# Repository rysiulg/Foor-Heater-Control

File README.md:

Own implementation
Foor Heater Control
with PCB based on triac and optotriac control

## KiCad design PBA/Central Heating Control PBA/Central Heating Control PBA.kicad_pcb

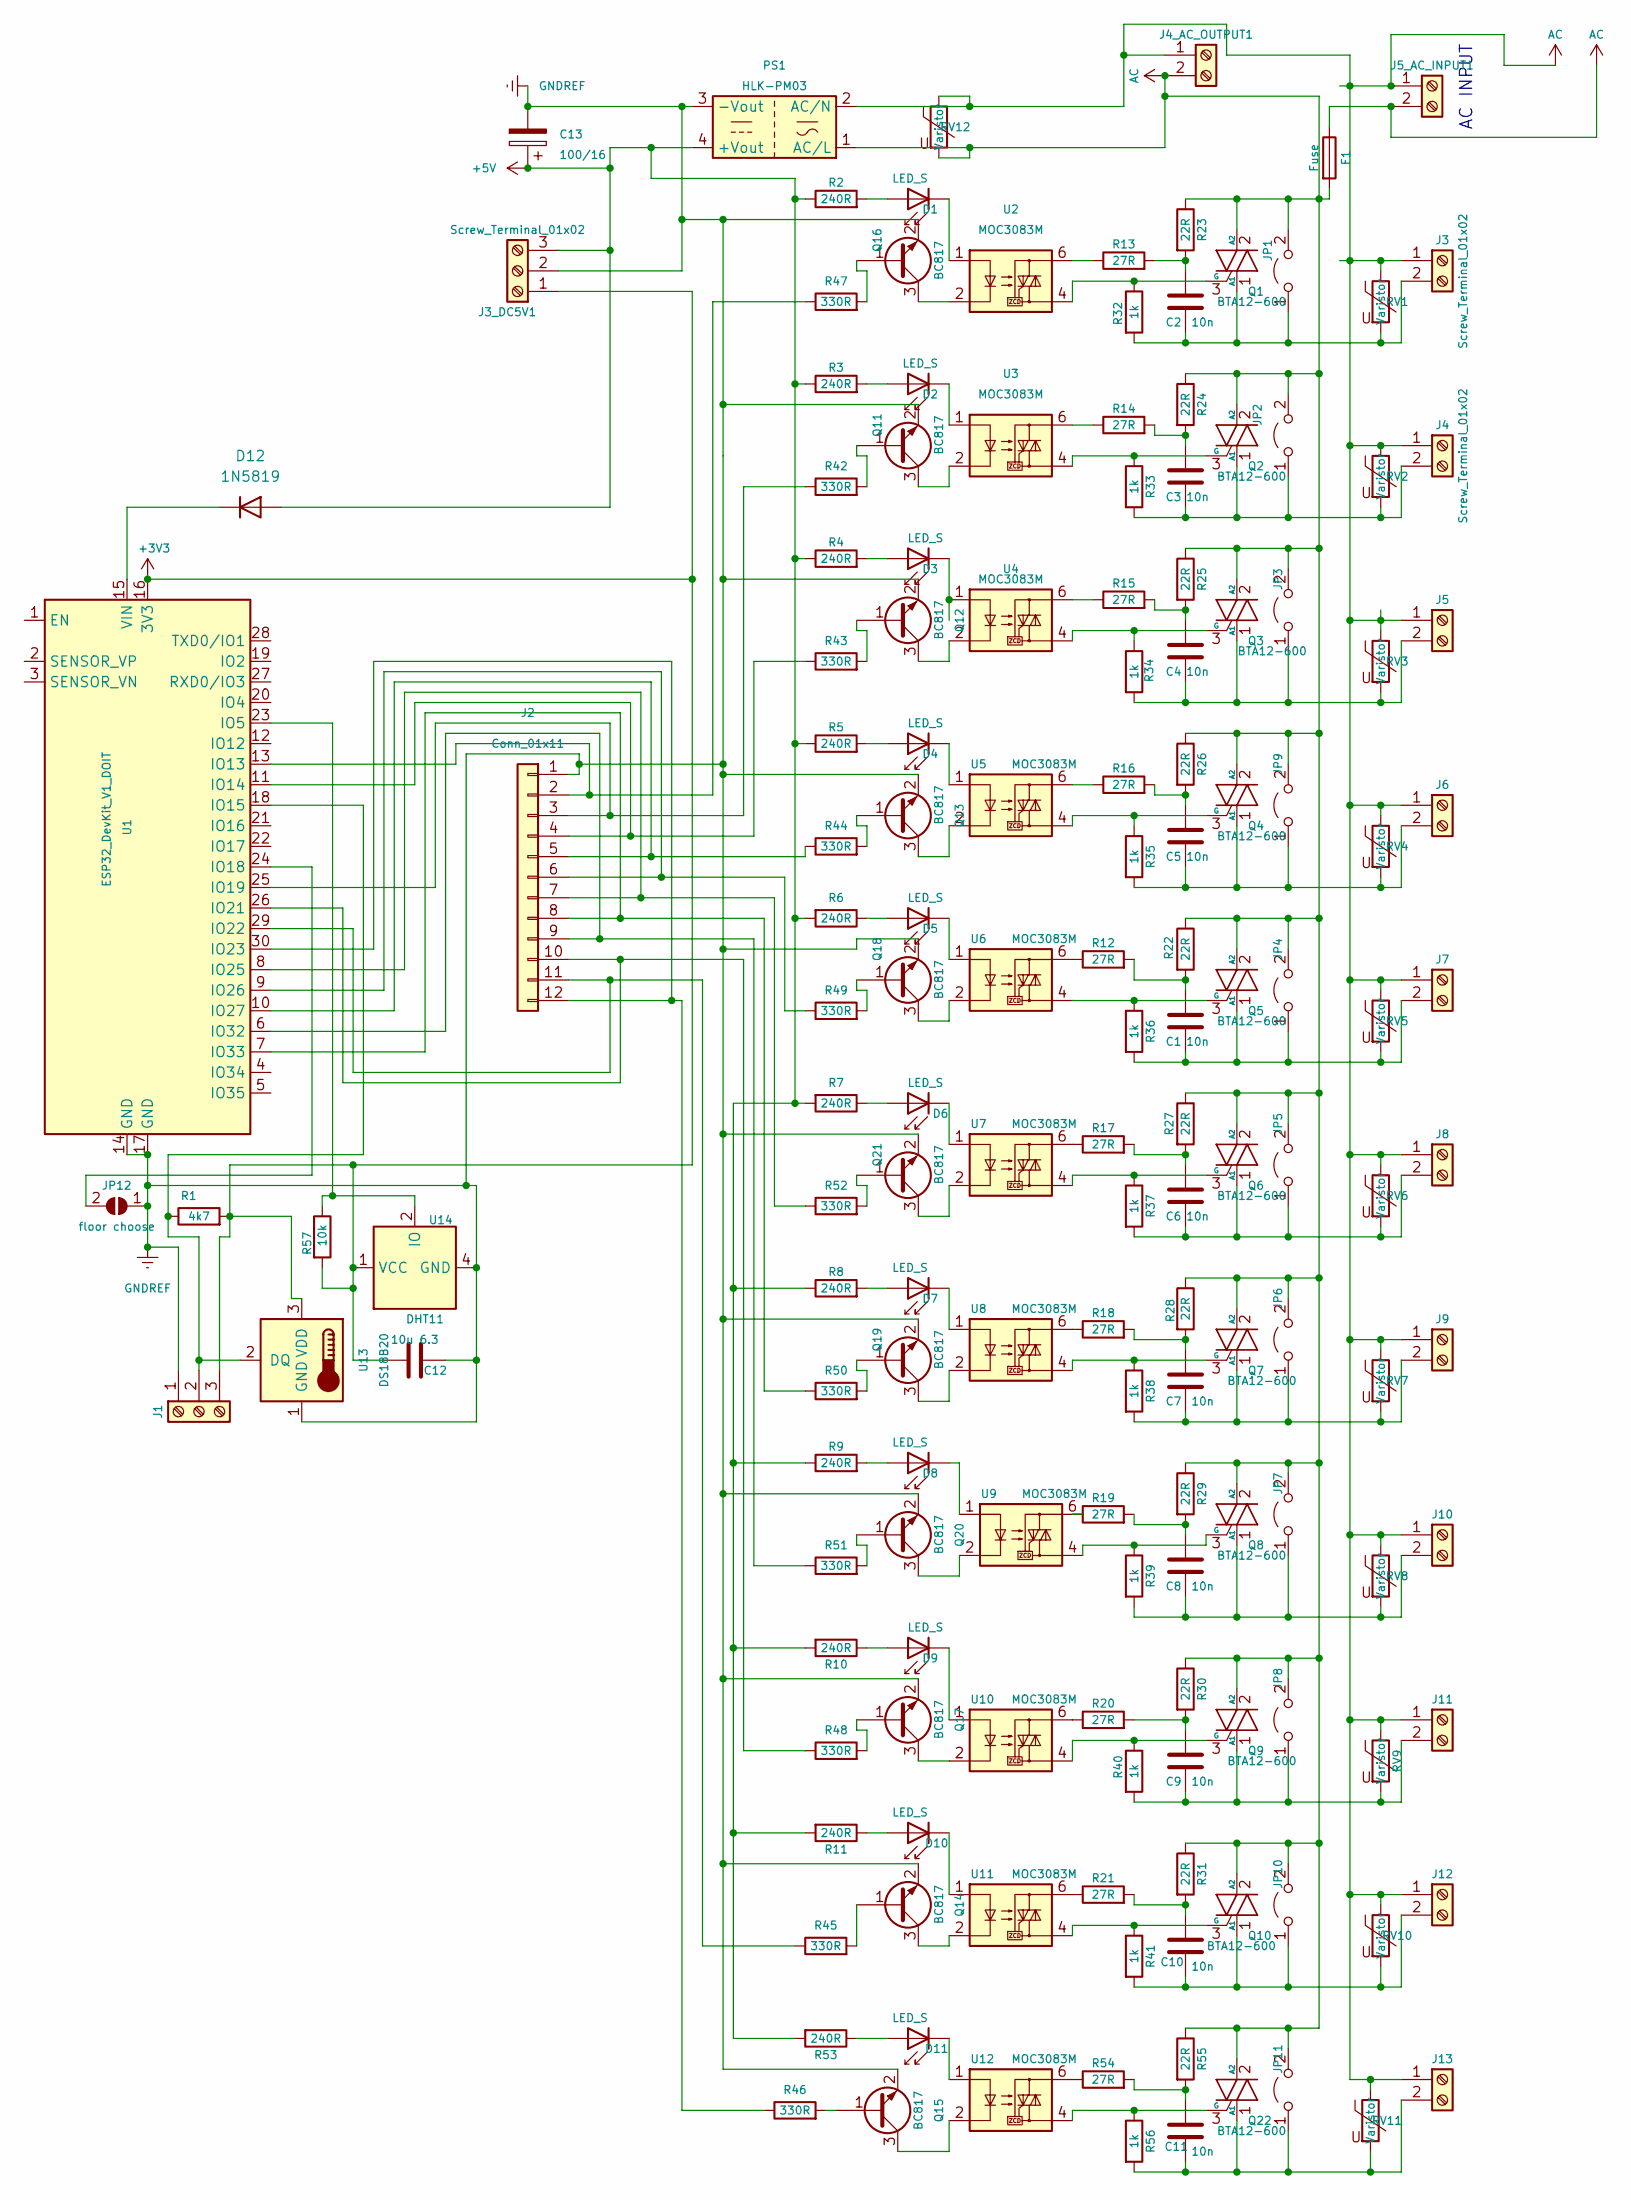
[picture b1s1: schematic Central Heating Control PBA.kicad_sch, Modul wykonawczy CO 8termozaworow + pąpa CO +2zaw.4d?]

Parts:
C1, C2, C3, C4, C5, C6, C7, C8, C9, C10, C11: 10n; C_Rect_L19.0mm_W7.0mm_P15.00mm_MKS4
C12: 10u 6.3; C_0805_2012Metric_Pad1.18x1.45mm_HandSolder
C13: 100/16; CP_Elec_6.3x5.9
D1, D2, D3, D4, D5, D6, D7, D8, D9, D10, D11: LED_S; LED_Rectangular_W3.0mm_H2.0mm
D12: 1N5819; D_SOD-123
F1: Fuse; Fuseholder_Littelfuse_100_series_5x20mm
J1: Screw_Terminal_01x03; TerminalBlock_MetzConnect_Type086_RT03403HBLC_1x03_P3.81mm_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
J2: Conn_01x11; PinHeader_1x12_P2.54mm_Vertical
J3, J4, J5, J6, J7, J8, J9, J10, J11, J12, J13: Screw_Terminal_01x02; TerminalBlock_MetzConnect_Type171_RT13702HBWC_1x02_P7.50mm_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
J3_DC5V1: Screw_Terminal_01x02; TerminalBlock_MetzConnect_Type073_RT02603HBLU_1x03_P5.08mm_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
J4_AC_OUTPUT1, J5_AC_INPUT1: Screw_Terminal_01x02; TerminalBlock_MetzConnect_Type101_RT01602HBWC_1x02_P5.08mm_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
JP1, JP2, JP3, JP4, JP5, JP6, JP7, JP8, JP9, JP10, JP11: Jumper_2_Open; PinSocket_1x02_P2.54mm_Vertical
JP12: floor choose; SolderJumper-2_P1.3mm_Open_TrianglePad1.0x1.5mm
PS1: HLK-PM03; Converter_ACDC_HiLink_HLK-PMxx
Q1, Q2, Q3, Q4, Q5, Q6, Q7, Q8, Q9, Q10, Q22: BTA12-600; TO-220-3_Vertical
Q11, Q12, Q13, Q14, Q15, Q16, Q17, Q18, Q19, Q20, Q21: BC817; SOT-23
R1: 4k7; R_0805_2012Metric_Pad1.20x1.40mm_HandSolder
R2, R3, R4, R5, R6, R7, R8, R9, R10, R11, R53: 240R; R_0805_2012Metric_Pad1.20x1.40mm_HandSolder
R12, R13, R14, R15, R16, R17, R18, R19, R20, R21, R54: 27R; R_Axial_DIN0207_L6.3mm_D2.5mm_P2.54mm_Vertical
R22, R23, R24, R25, R26, R27, R28, R29, R30, R31, R55: 22R; R_Axial_DIN0207_L6.3mm_D2.5mm_P2.54mm_Vertical
R32, R33, R34, R35, R36, R37, R38, R39, R40, R41, R56: 1k; R_Axial_DIN0207_L6.3mm_D2.5mm_P2.54mm_Vertical
R42, R43, R44, R45, R46, R47, R48, R49, R50, R51, R52: 330R; R_0805_2012Metric_Pad1.20x1.40mm_HandSolder
R57: 10k; R_0805_2012Metric_Pad1.20x1.40mm_HandSolder
RV1, RV2, RV3, RV4, RV5, RV6, RV7, RV8, RV9, RV10, RV11, RV12: Varistor; RV_Disc_D9mm_W3.3mm_P5mm-hole0.9
U1: ESP32_DevKit_V1_DOIT; esp32_devkit_v1_doit
U2, U3, U4, U5, U6, U7, U8, U9, U10, U11, U12: MOC3083M; DIP-6_W7.62mm_LongPads_MOC3803
U13: DS18B20; TO-92_Inline_W4.0mm_Horizontal_FlatSideDown
U14: DHT11; Aosong_DHT11_5.5x12.0_P2.54mm

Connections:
+3V3: C12.2, J1.3, J3_DC5V1.1, R1.2, R57.2, U1.16 (3V3), U13.3 (VDD), U14.1 (VCC)
+5V: C13.1, D12.2 (A), J3_DC5V1.3, PS1.4 (+Vout), R2.1, R3.1, R4.1, R5.1, R6.2, R7.2, R8.1, R9.1, R10.2, R11.2, R53.2
GNDREF: C12.1, C13.2, J1.1, J2.1, J3_DC5V1.2, JP12.1 (A), PS1.3 (-Vout), Q11.2 (E), Q12.2 (E), Q13.2 (E), Q14.2 (E), Q15.2 (E), Q16.2 (E), Q17.2 (E), Q18.2 (E), Q19.2 (E), Q20.2 (E), Q21.2 (E), U1.14 (GND), U1.17 (GND), U13.1 (GND), U14.4 (GND)
unnamed: C1.1, R12.2, R22.2
unnamed: C1.2, J7.2, JP4.1 (A), Q5.1 (A1), R36.2, RV5.2
unnamed: C2.1, R13.2, R23.2
unnamed: C2.2, J3.2, JP1.1 (A), Q1.1 (A1), R32.2, RV1.2
unnamed: C3.1, R14.2, R24.2
unnamed: C3.2, J4.2, JP2.1 (A), Q2.1 (A1), R33.2, RV2.2
unnamed: C4.1, R15.2, R25.2
unnamed: C4.2, J5.2, JP3.1 (A), Q3.1 (A1), R34.2, RV3.2
unnamed: C5.1, R16.2, R26.2
unnamed: C5.2, J6.2, JP9.1 (A), Q4.1 (A1), R35.2, RV4.2
unnamed: C6.1, R17.2, R27.2
unnamed: C6.2, J8.2, JP5.1 (A), Q6.1 (A1), R37.2, RV6.2
unnamed: C7.1, R18.2, R28.2
unnamed: C7.2, J9.2, JP6.1 (A), Q7.1 (A1), R38.2, RV7.2
unnamed: C8.1, R19.2, R29.2
unnamed: C8.2, J10.2, JP7.1 (A), Q8.1 (A1), R39.2, RV8.2
unnamed: C9.1, R20.2, R30.2
unnamed: C9.2, J11.2, JP8.1 (A), Q9.1 (A1), R40.2, RV9.2
unnamed: C10.1, R21.2, R31.2
unnamed: C10.2, J12.2, JP10.1 (A), Q10.1 (A1), R41.2, RV10.2
unnamed: C11.1, R54.2, R55.2
unnamed: C11.2, J13.2, JP11.1 (A), Q22.1 (A1), R56.2, RV11.2
unnamed: D1.1 (K), U2.1
unnamed: D1.2 (A), R2.2
unnamed: D2.1 (K), U3.1
unnamed: D2.2 (A), R3.2
unnamed: D3.1 (K), U4.1
unnamed: D3.2 (A), R4.2
unnamed: D4.1 (K), U5.1
unnamed: D4.2 (A), R5.2
unnamed: D5.1 (K), U6.1
unnamed: D5.2 (A), R6.1
unnamed: D6.1 (K), U7.1
unnamed: D6.2 (A), R7.1
unnamed: D7.1 (K), U8.1
unnamed: D7.2 (A), R8.2
unnamed: D8.1 (K), U9.1
unnamed: D8.2 (A), R9.2
unnamed: D9.1 (K), U10.1
unnamed: D9.2 (A), R10.1
unnamed: D10.1 (K), U11.1
unnamed: D10.2 (A), R11.1
unnamed: D11.1 (K), U12.1
unnamed: D11.2 (A), R53.1
unnamed: D12.1 (K), U1.15 (VIN)
unnamed: J1.2, R1.1, U1.18 (IO15), U13.2 (DQ)
unnamed: J2.2, R47.1, U1.13 (IO13)
unnamed: J2.3, R42.1, U1.25 (IO19)
unnamed: J2.4, R43.1, U1.11 (IO14)
unnamed: J2.5, R44.1, U1.10 (IO27)
unnamed: J2.6, R49.1, U1.9 (IO26)
unnamed: J2.7, R52.1, U1.8 (IO25)
unnamed: J2.8, R50.1, U1.7 (IO33)
unnamed: J2.9, R51.1, U1.6 (IO32)
unnamed: J2.10, R48.1, U1.26 (IO21)
unnamed: J2.11, R45.1, U1.29 (IO22)
unnamed: J2.12, R46.1, U1.30 (IO23)
unnamed: JP12.2 (B), U1.24 (IO18)
unnamed: Q1.3 (G), R32.1, U2.4
unnamed: Q2.3 (G), R33.1, U3.4
unnamed: Q3.3 (G), R34.1, U4.4
unnamed: Q4.3 (G), R35.1, U5.4
unnamed: Q5.3 (G), R36.1, U6.4
unnamed: Q6.3 (G), R37.1, U7.4
unnamed: Q7.3 (G), R38.1, U8.4
unnamed: Q8.3 (G), R39.1, U9.4
unnamed: Q9.3 (G), R40.1, U10.4
unnamed: Q10.3 (G), R41.1, U11.4
unnamed: Q11.1 (B), R42.2
unnamed: Q11.3 (C), U3.2
unnamed: Q12.1 (B), R43.2
unnamed: Q12.3 (C), U4.2
unnamed: Q13.1 (B), R44.2
unnamed: Q13.3 (C), U5.2
unnamed: Q14.1 (B), R45.2
unnamed: Q14.3 (C), U11.2
unnamed: Q15.1 (B), R46.2
unnamed: Q15.3 (C), U12.2
unnamed: Q16.1 (B), R47.2
unnamed: Q16.3 (C), U2.2
unnamed: Q17.1 (B), R48.2
unnamed: Q17.3 (C), U10.2
unnamed: Q18.1 (B), R49.2
unnamed: Q18.3 (C), U6.2
unnamed: Q19.1 (B), R50.2
unnamed: Q19.3 (C), U8.2
unnamed: Q20.1 (B), R51.2
unnamed: Q20.3 (C), U9.2
unnamed: Q21.1 (B), R52.2
unnamed: Q21.3 (C), U7.2
unnamed: Q22.3 (G), R56.1, U12.4
unnamed: R12.1, U6.6
unnamed: R13.1, U2.6
unnamed: R14.1, U3.6
unnamed: R15.1, U4.6
unnamed: R16.1, U5.6
unnamed: R17.1, U7.6
unnamed: R18.1, U8.6
unnamed: R19.1, U9.6
unnamed: R20.1, U10.6
unnamed: R21.1, U11.6
unnamed: R54.1, U12.6
unnamed: R57.1, U1.23 (IO5), U14.2 (IO)

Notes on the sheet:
AC INPUT

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
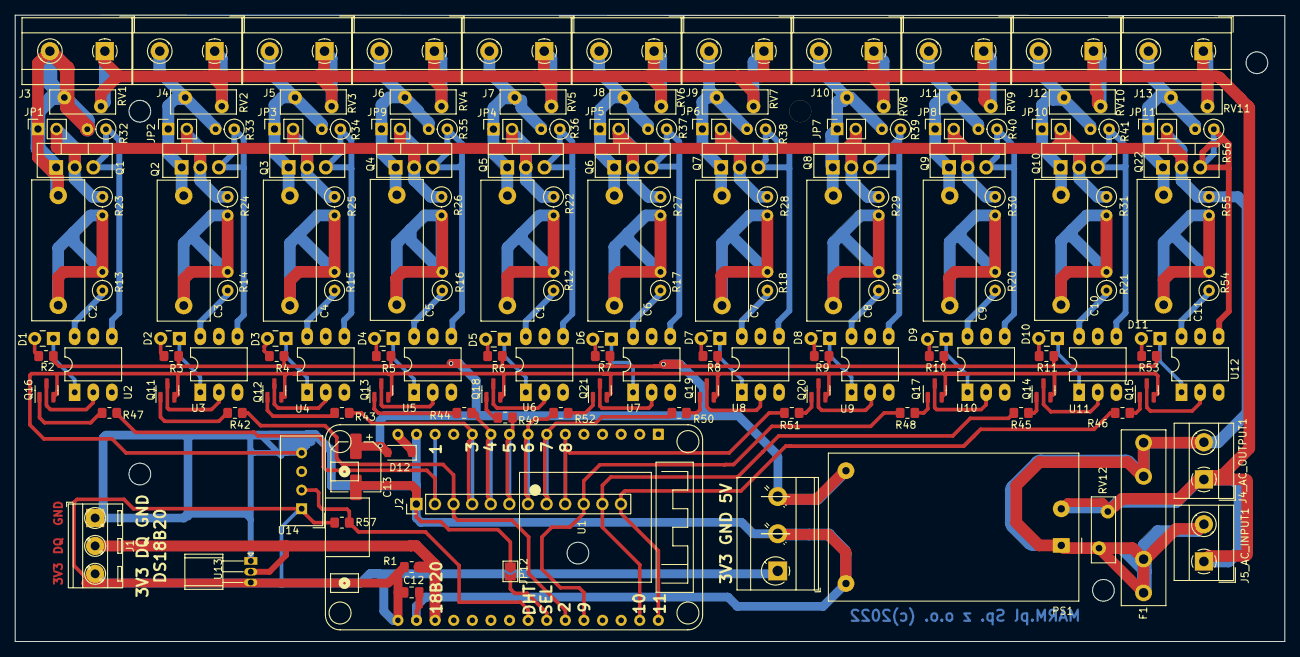
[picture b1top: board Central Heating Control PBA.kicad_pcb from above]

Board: 2 copper layers, 173.4 x 85.5 mm, 160 parts (0 on the bottom side), 108 nets.

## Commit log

2022-05-07 Initial commit v.2
2022-05-07 Create plot
2022-05-07 Initial
2022-05-07 sync
2022-05-07 update files
2022-05-07 back
2022-05-08 update -increase time send data
2022-05-08 corrective update on mqtt received datas
2022-05-08 corrections of set topics
2022-05-09 add more sensors to mqtt subscribe
2022-05-10 Update PBA for DHT22 and footprints... Removed ArduinoJson adding getJsonVal function recuces about 4k of code for only read json value
2022-05-23 add webserial TOGGLEPUMP
2022-05-23 added hall reading ;)
2022-05-24 corrections
2022-05-24 update time
2022-05-24 update mqtt news topic
2022-05-24 uptade githubignore
2022-05-29 pba and code update
2022-06-05 update save routine to save only after change
2022-06-10 update pin assigments and change ledlamp behavior to blink every 2 sec when connected
2022-06-10 remove ledpin from pump place ;)
2022-06-12 update web...
2022-06-13 add dht values to mqtt and influx
2022-06-13 update min and max roomtemp avg -remove total min and total max values form min and max when no data
2022-06-13 update -remove roomtemplo if no data
2022-06-13 add restart if after 15min no mqtt connection -assume something wrong with wifi?
2022-06-13 add 30sec delay according to news update time to bypass mqtt reconnect -maybe .isconnected() is broken?
2022-06-27 Changes to be committed: modified: platformio.ini deleted: src/backtrace_decode.txt modified: src/config-translate.h modified: src/config.h modified: src/configmqtttopics.h modified: src/dane.h modif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
    Untracked files:
    get-pip.py
    lib/ESPAsyncWebServer-esphome/src/ESPAsyncWebServer.h.bak
    lib/LittleFS_esp32/
    src/backtrace_decode.bat
    src/backtrace_decode.bat.bak
2022-08-02 change interface, change to asyncmqtt and wifi events and + doublereset detect and littlefs for web files and config
2022-09-26 update pump logic and www mark card active status
2024-10-22 Create n
2024-10-22 Update n
2024-10-22 Rename n to update_version.py

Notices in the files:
PBA/Central Heating Control PBA/Central Heating Control PBA.kicad_pcb:
MARM.pl Sp. z o.o. (c)2022
MARM.pl Sp. z o.o. (c)2022 v.2.1
